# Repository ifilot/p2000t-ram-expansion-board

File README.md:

# P2000T RAM expansion board

## Table of contents

* [Purpose](#purpose)
* [Memory lay-out](#memory-lay-out)
* [Installation](#installation)
* [Testing the expansion board](#testing-the-expansion-board)
* [Schematic](#schematic)
* [Bill of materials](#bill-of-materials)
* [Testing bank switching in BASIC](#testing-bank-switching-in-basic)
* [Files](#files)
* [Alternative RAM expansions](#alternative-ram-expansions)
  * [SMD-128KiB version](#smd-128kib-version)
  * [SMD-CPLD-128KiB version](#smd-cpld-128kib-version)
  * [SMD-CPLD-512KiB version](#smd-cpld-512kib-version)
  * [THT-1056 KiB expansion](#tht-1056-kib-expansion)
  * [THT-2080 KiB expansion](#tht-2080-kib-expansion)
* [License](#license)

> [!TIP] 
> Have questions or comments about the **P2000T RAM expansion**? Join
> the conversation and chat with the developers on our [Discord
> server](https://discord.gg/YtzJTWYAxy).

## Purpose

This repository provides several RAM expansion boards for the Philips P2000T,
ranging from 64 KiB to over 2 MiB. Options vary in complexity (THT, SMD, CPLD),
so choose a board that fits your soldering skills and tools. A RAM tester
utility is included to verify proper installation and functionality after
assembly.

> [!IMPORTANT]
> This repository includes various RAM expansion PCBs for the P2000T. Your
> choice should depend on your soldering skills (THT or SMD) and available
> tools (e.g. CPLD programmer). Review this README to find a board that
> matches your comfort level before starting a build. 

## Memory lay-out

The memory lay-out of the P2000T is organized as shown in the table below

| Address       | Description      |
| ------------- | ---------------- |
| 0x0000-0x1000 | Monitor rom      |
| 0x1000-0x4FFF | Cartridge        |
| 0x5000-0x5FFF | Video memory     |
| 0x6000-0x9FFF | RAM memory       |
| 0xA000-0xDFFF | 16 KiB expansion |
| 0xE000-0xFFFF | 8 KiB banks      |

For the default 16 KiB stock model, only the memory at `0x6000-0x9FFF` is
available. The most simple expansion board adds 64k memory such that an
additional 16 KiB of RAM is available at `0xA000-0xDFFF` and another 48 KiB
using bank switching. Bank switching means that you can only access 8 KiB of the
48 KiB at a time, depending on the value of a register which can be accessed via
an `OUT` instruction at `0x94`. This register can hold values of `0-5`,
amounting to 6x8 KiB = 48 KiB of bankable memory.

## Installation

To install the expansion board, you need to plug in the expansion board on the
corresponding expansion 2x20 male pin header on the male board. This pin header
is found directly behind the cartridge slots. Furthermore, you need to solder
a GND and a 5V line onto the power PCB (see image below) and insert that in the
screw terminal of the expansion board.

> [!WARNING]  
> Please check carefully that the polarity is correct. Although the board comes
> with reverse polarity protection in the form of a diode, it is always better
> to check twice before turning on the power.

In the image below, you see a GND (black) and a 5V (red) line attached to the
power PCB. Please ensure you solder the lines to the correct pins and check
with a multimeter before connecting to the RAM expansion board.

Consult the image below for the correct voltages between the pins.

> [!WARNING]  
> Please check with a multimeter that you did not short-circuit any of the power
> lines on the POWER PCB. Please check this at least two times before turning on
> your P2000T. Short-circuiting of any of the power rails can cause permanent
> damage your machine.

## Testing the expansion board

This repository comes bundled with a RAM testing utility. Write the RAM testing
utility to a SLOT1 cartridge and boot your P2000T with this program in SLOT1.
The RAM testing utility will perform an extensive test of the memory and show
any errors it encounters.

## Schematic

The schematic for the RAM expansion board is shown below. The ram expansion
board essentially hosts two 32 KiB RAM chips and a bank register. Using a small
set of additional logic chips, the line decoding and bank switching is handled.

## Bill of materials

* 1x74HC00 (quad NAND-gate)
* 1x74HC04 (hex inverter)
* 1x74HC32 (quad OR-gate)
* 1x74HC157 (quad 2-input multiplexer)
* 1x74HC173 (quad positive edge triggered D-type flip-flop)
* 1x74HC688 (8-bit magnitude comparator)
* 1x74HC245 (octal bus transceiver)
* 2x62256 (32 KiB SRAM)
* 1x220uF capacitor (100uF also works)
* 8x0.1uF capacitor
* 1x1N4148 diode
* 1x 40 pin female pin header (2x20 pins; 2.54mm spacing)
* 1x screw terminal

**Unpopulated PCB**

**Populated PCB**

## Testing bank switching in BASIC

If you want to test the bank switching functionality in BASIC, you can use
the following instructions after booting the machine.

First, we need to set the top of BASIC to `0x9000`.

```
CLEAR 50,&H9000
```

The reason we do this is to ensure that the stack is not residing at the top 8
KiB because those bytes will become inaccessible after bank switching. Next, we
will first write a value to memory address `0xE000`, check that this value is
properly written, change to another bank and read from the same memory address.
A different value should be returned (typically 0). Next, we write a different
value to the `0xE000` and change bank to the initial bank. The original value
should now be correctly retrieved. The procedure is performed using the
following (very small) snippet of BASIC code.

```
10 POKE &HE000,42
20 PRINT(PEEK(&HE000))
30 OUT &H94,1
40 PRINT(PEEK(&HE000))
50 POKE &HE000,43
60 OUT &H94,0
70 PRINT(PEEK(&HE000))
```
After entering in these instructions, type `RUN`. The output of this code should
be something similar to the code as shown below. The second value might be
potentially different, depending on earlier memory operations, though is
expected to be a zero on a fresh boot of the machine.

```
42
0
42
```

## Files

* [KiCad schematics](pcb/p2000t-ram-expansion-board)
* [RAM tester utility](ramtester)

## Alternative RAM expansions

### SMD-128KiB version

Next to the 64 KiB memory expansion using
[DIP](https://en.wikipedia.org/wiki/Dual_in-line_package) chips, there is also a
128 KiB memory expansion using
[SMD](https://en.wikipedia.org/wiki/Surface-mount_technology) chips. Because of
the typical lower price of this last category of chips, this memory expansion is
a bit cheaper to produce. It does require you to be proficient in soldering on
SMD components.

The 128 KiB memory expansion uses a single `CY62128ELL-45SX` 128 KiB memory
chip. The lower 16 KiB of this chip can be accessed at `0xA000-0xDFFF`. The
remaining 112 KiB are available as 14 banks of 8 KiB each at `0xE000-0xFFFF`.
Similar to the other memory expansion boards, bank switching proceeds by writing
a value to I/O port `0x94`. One can also read back the current bank from this
port.

The source files for this board can be found
[here](pcb/p2000t-ram-expansion-board-128kb-smd/).

**Unpopulated PCB**

**Populated PCB**

**Installed PCB**

### SMD-CPLD-128KiB version

To cut down costs even further, there is also a CUPL version. Besides the
`CY62128ELL-45SX`, the PCB only hosts one other chip: a `ATF1502`. All glue
logic required for the RAM expansion board is basically programmed on this chip.

The source files for this board can be found
[here](pcb/p2000t-ram-expansion-board-128-512-smd-cpld).

**Unpopulated PCB**

**Populated PCB**

### SMD-CPLD-512KiB version

Moving beyond the 128 KiB limit, there is also a versatile SMD-type board
that admits 1-4 `CY62128ELL-45SX` 128 KiB memory chips.

The source files for this board can be found
[here](pcb/p2000t-ram-expansion-board-128-512-smd-cpld).

**Installed PCB**

**Populated PCB**

### THT-1056 KiB expansion

This board uses a single 32 KiB static RAM chip to provide 2x16 KiB on
`0xA000-0xDFFF` and two 512 KiB static RAM chips to provide another 128x8 KiB on
`0xE000-0xFFFF`. The way this board works is very similar to the regular 64 KiB
board. The highest bit in the bank register toggle the 16 KiB banking while the
lower 7 bits provide the banking for the 8 KiB of memory.

The source files for this board can be found
[here](pcb/p2000t-ram-expansion-board-1056kb/).

**Unpopulated PCB**

**Populated PCB**

**Installed PCB**

### THT-2080 KiB expansion

This board uses a single 32 KiB static RAM chip to provide 2x16 KiB on
`0xA000-0xDFFF` and four 512 KiB static RAM chips to provide another 256x8 KiB
on `0xE000-0xFFFF`. This board requires two bank registers, one 8-bit bank
register exposed on I/O port `0x94` and another two-bit bank register on I/O
port `0x95` (only one bit of the two-bit bank register is used).

The source files for this board can be found
[here](pcb/p2000t-ram-expansion-board-2080kb/).

**Populated PCB**

**Installed PCB**

## License

* All source code, i.e. the [ram tester utility](ramtester)
  are released under a [GPLv3 license](https://www.gnu.org/licenses/gpl-3.0.html).
* The hardware files (KiCad schematics) are released under the 
  [CC BY-SA 4.0](https://creativecommons.org/licenses/by-sa/4.0/) license.

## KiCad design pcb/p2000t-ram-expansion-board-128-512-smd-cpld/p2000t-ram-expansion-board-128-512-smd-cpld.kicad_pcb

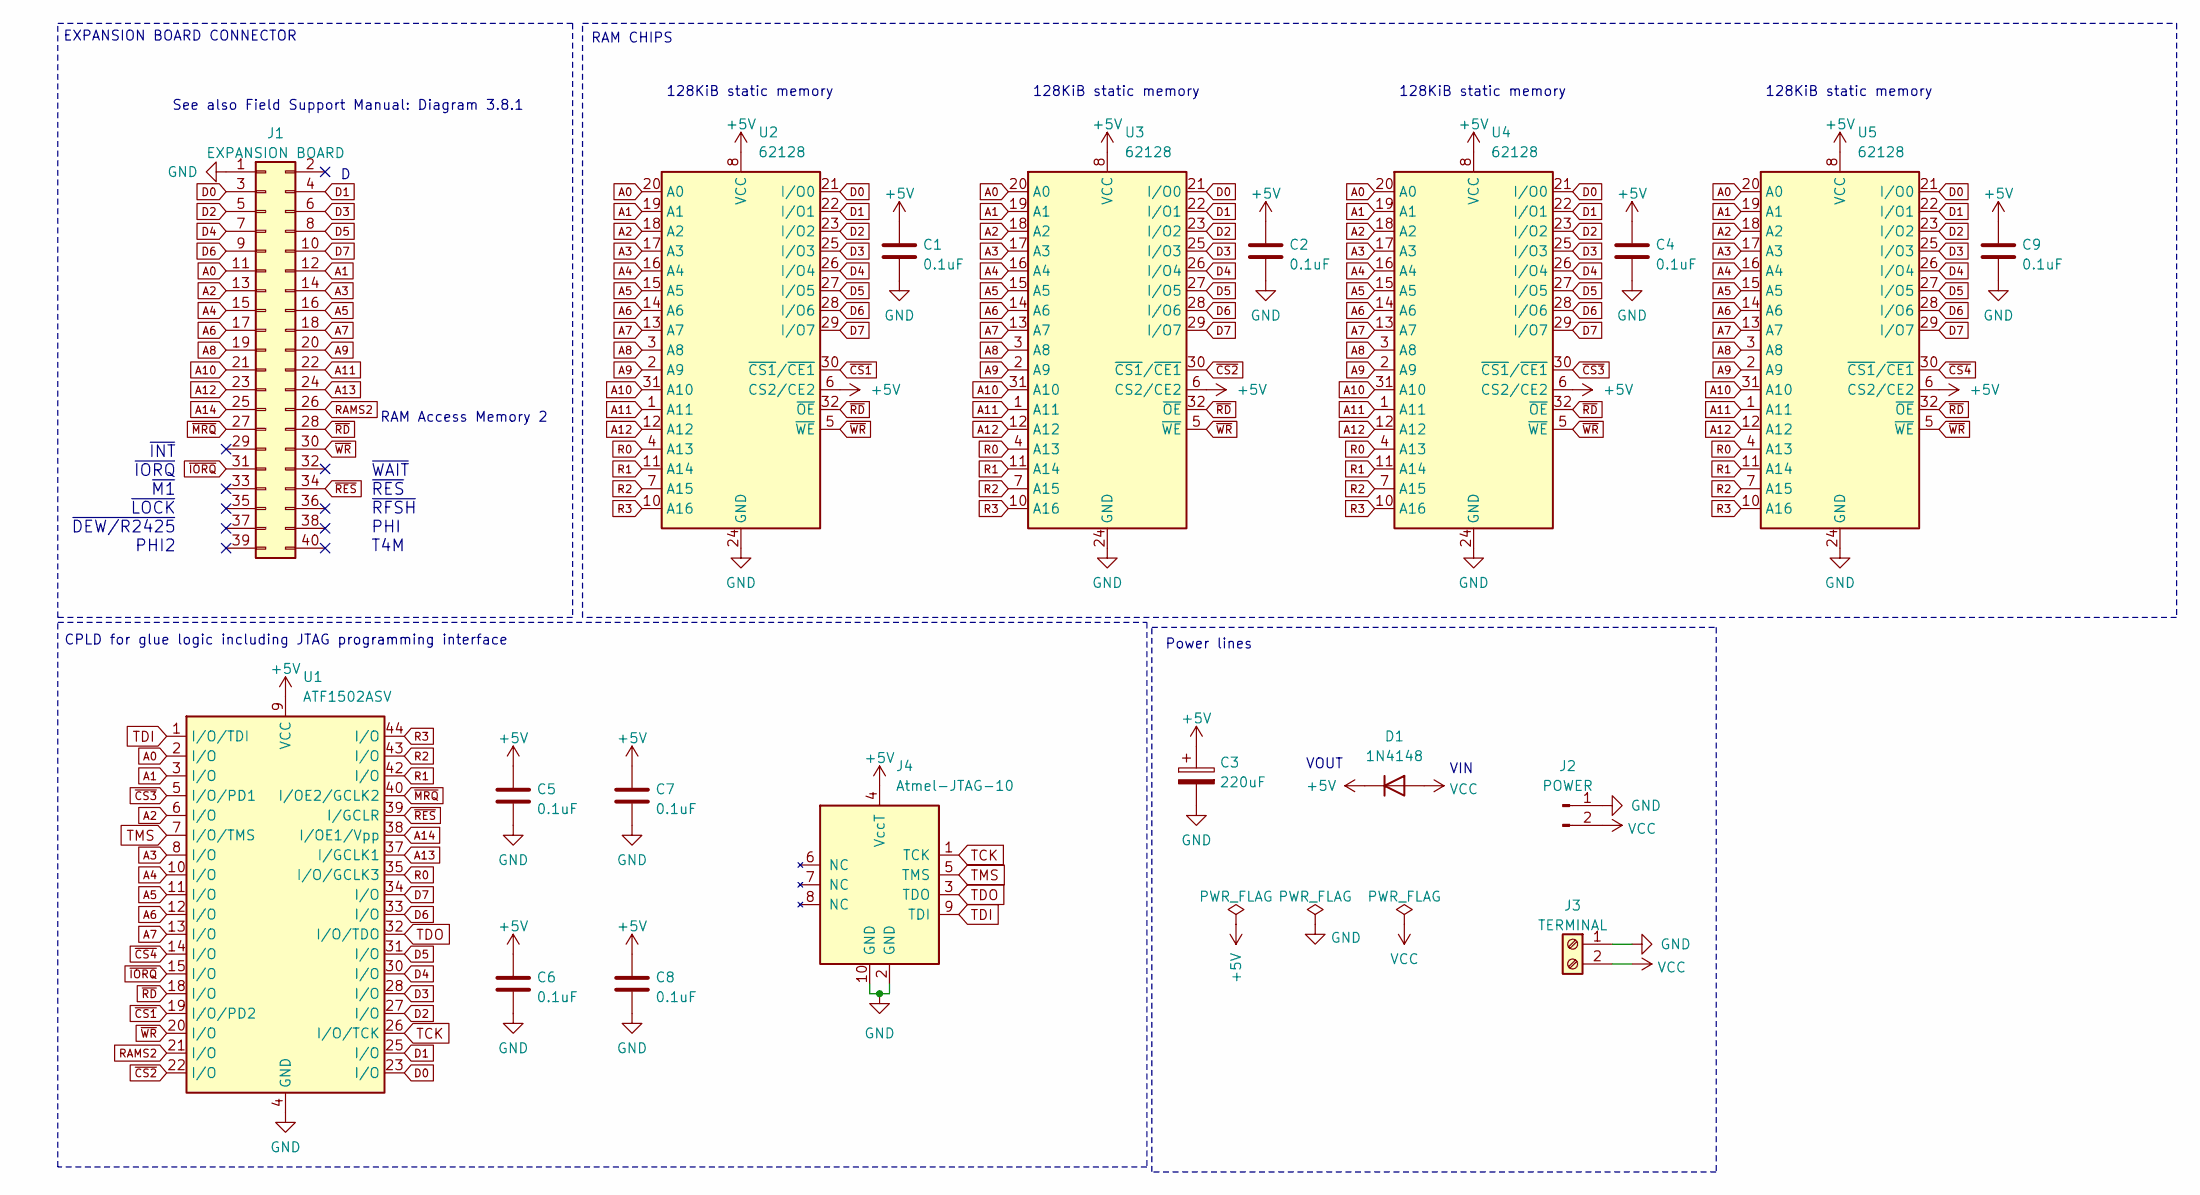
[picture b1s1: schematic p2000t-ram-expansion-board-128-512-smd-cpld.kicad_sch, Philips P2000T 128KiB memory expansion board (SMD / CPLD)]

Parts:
C1, C2, C4, C5, C6, C7, C8, C9: 0.1uF; C_0805_2012Metric_Pad1.18x1.45mm_HandSolder; LCSC Part # C126469
C3: 220uF; CP_Radial_D6.3mm_P2.50mm
D1: 1N4148; D_DO-35_SOD27_P7.62mm_Horizontal
J1: EXPANSION BOARD; PinHeader_2x20_P2.54mm_Vertical
J2: POWER; PinSocket_1x02_P2.54mm_Vertical
J3: TERMINAL; TerminalBlock_bornier-2_P5.08mm
J4: Atmel-JTAG-10; IDC-Header_2x05_P2.54mm_Vertical
U1: ATF1502ASV; TQFP-44_10x10mm_P0.8mm
U2, U3, U4, U5: 62128; TSOP-I-32_18.4x8mm_P0.5mm; LCSC Part # C2840304

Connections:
+5V: C1.1, C2.1, C3.1, C4.1, C5.1, C6.1, C7.1, C8.1, C9.1, D1.1 (K), J4.4 (VccT), U1.9 (VCC), U1.17 (VCC), U1.29 (VCC), U1.41 (VCC), U2.6 (CS2/CE2), U2.8 (VCC), U3.6 (CS2/CE2), U3.8 (VCC), U4.6 (CS2/CE2), U4.8 (VCC), U5.6 (CS2/CE2), U5.8 (VCC)
A0: J1.11, U1.2 (I/O), U2.20 (A0), U3.20 (A0), U4.20 (A0), U5.20 (A0)
A1: J1.12, U1.3 (I/O), U2.19 (A1), U3.19 (A1), U4.19 (A1), U5.19 (A1)
A2: J1.13, U1.6 (I/O), U2.18 (A2), U3.18 (A2), U4.18 (A2), U5.18 (A2)
A3: J1.14, U1.8 (I/O), U2.17 (A3), U3.17 (A3), U4.17 (A3), U5.17 (A3)
A4: J1.15, U1.10 (I/O), U2.16 (A4), U3.16 (A4), U4.16 (A4), U5.16 (A4)
A5: J1.16, U1.11 (I/O), U2.15 (A5), U3.15 (A5), U4.15 (A5), U5.15 (A5)
A6: J1.17, U1.12 (I/O), U2.14 (A6), U3.14 (A6), U4.14 (A6), U5.14 (A6)
A7: J1.18, U1.13 (I/O), U2.13 (A7), U3.13 (A7), U4.13 (A7), U5.13 (A7)
A8: J1.19, U2.3 (A8), U3.3 (A8), U4.3 (A8), U5.3 (A8)
A9: J1.20, U2.2 (A9), U3.2 (A9), U4.2 (A9), U5.2 (A9)
A10: J1.21, U2.31 (A10), U3.31 (A10), U4.31 (A10), U5.31 (A10)
A11: J1.22, U2.1 (A11), U3.1 (A11), U4.1 (A11), U5.1 (A11)
A12: J1.23, U2.12 (A12), U3.12 (A12), U4.12 (A12), U5.12 (A12)
A13: J1.24, U1.37 (I/GCLK1)
A14: J1.25, U1.38 (I/OE1/Vpp)
D0: J1.3, U1.23 (I/O), U2.21 (I/O0), U3.21 (I/O0), U4.21 (I/O0), U5.21 (I/O0)
D1: J1.4, U1.25 (I/O), U2.22 (I/O1), U3.22 (I/O1), U4.22 (I/O1), U5.22 (I/O1)
D2: J1.5, U1.27 (I/O), U2.23 (I/O2), U3.23 (I/O2), U4.23 (I/O2), U5.23 (I/O2)
D3: J1.6, U1.28 (I/O), U2.25 (I/O3), U3.25 (I/O3), U4.25 (I/O3), U5.25 (I/O3)
D4: J1.7, U1.30 (I/O), U2.26 (I/O4), U3.26 (I/O4), U4.26 (I/O4), U5.26 (I/O4)
D5: J1.8, U1.31 (I/O), U2.27 (I/O5), U3.27 (I/O5), U4.27 (I/O5), U5.27 (I/O5)
D6: J1.9, U1.33 (I/O), U2.28 (I/O6), U3.28 (I/O6), U4.28 (I/O6), U5.28 (I/O6)
D7: J1.10, U1.34 (I/O), U2.29 (I/O7), U3.29 (I/O7), U4.29 (I/O7), U5.29 (I/O7)
GND: C1.2, C2.2, C3.2, C4.2, C5.2, C6.2, C7.2, C8.2, C9.2, J1.1, J2.1, J3.1, J4.2 (GND), J4.10 (GND), U1.4 (GND), U1.16 (GND), U1.24 (GND), U1.36 (GND), U2.24 (GND), U3.24 (GND), U4.24 (GND), U5.24 (GND)
R0: U1.35 (I/O/GCLK3), U2.4 (A13), U3.4 (A13), U4.4 (A13), U5.4 (A13)
R1: U1.42 (I/O), U2.11 (A14), U3.11 (A14), U4.11 (A14), U5.11 (A14)
R2: U1.43 (I/O), U2.7 (A15), U3.7 (A15), U4.7 (A15), U5.7 (A15)
R3: U1.44 (I/O), U2.10 (A16), U3.10 (A16), U4.10 (A16), U5.10 (A16)
RAMS2: J1.26, U1.21 (I/O)
TCK: J4.1 (TCK), U1.26 (I/O/TCK)
TDI: J4.9 (TDI), U1.1 (I/O/TDI)
TDO: J4.3 (TDO), U1.32 (I/O/TDO)
TMS: J4.5 (TMS), U1.7 (I/O/TMS)
VCC: D1.2 (A), J2.2, J3.2
~CS1: U1.19 (I/O/PD2), U2.30 (~CS1/~CE1)
~CS2: U1.22 (I/O), U3.30 (~CS1/~CE1)
~CS3: U1.5 (I/O/PD1), U4.30 (~CS1/~CE1)
~CS4: U1.14 (I/O), U5.30 (~CS1/~CE1)
~IORQ: J1.31, U1.15 (I/O)
~MRQ: J1.27, U1.40 (I/OE2/GCLK2)
~RD: J1.28, U1.18 (I/O), U2.32 (~OE), U3.32 (~OE), U4.32 (~OE), U5.32 (~OE)
~RES: J1.34, U1.39 (I/GCLR)
~WR: J1.30, U1.20 (I/O), U2.5 (~WE), U3.5 (~WE), U4.5 (~WE), U5.5 (~WE)

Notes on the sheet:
128KiB static memory
VIN
EXPANSION BOARD CONNECTOR
VOUT
~{INT} ~{IORQ} ~{M1} ~{LOCK} ~{DEW/R2425} PHI2
RAM Access Memory 2
RAM CHIPS
See also Field Support Manual: Diagram 3.8.1
Power lines
~{WAIT} ~{RES} ~{RFSH} PHI T4M
CPLD for glue logic including JTAG programming interface

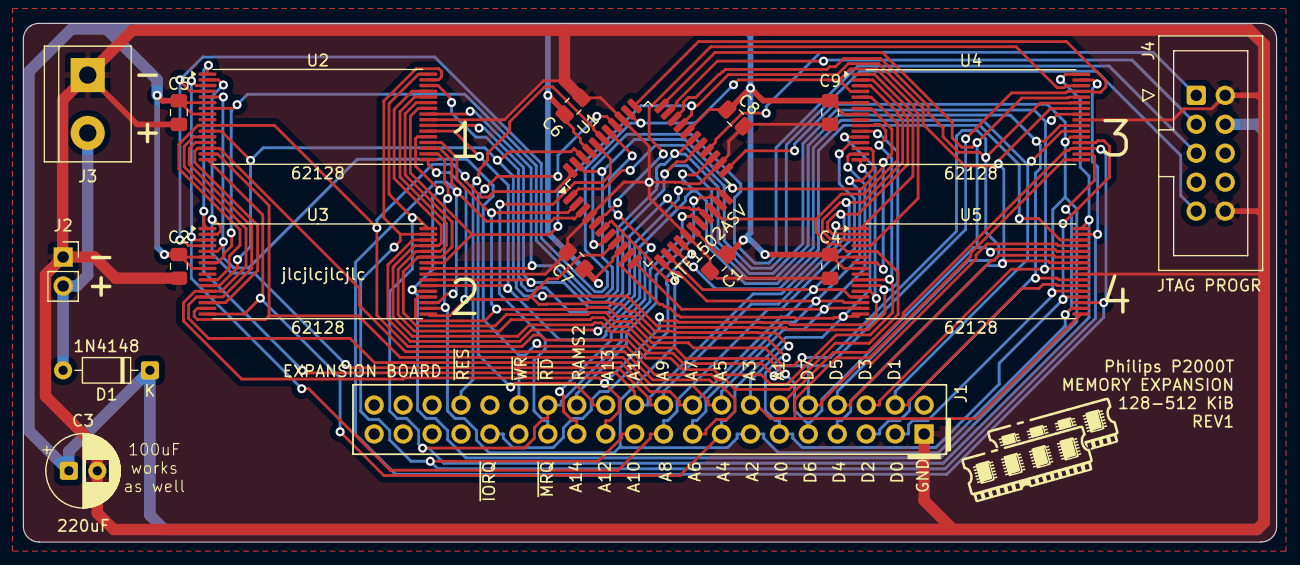
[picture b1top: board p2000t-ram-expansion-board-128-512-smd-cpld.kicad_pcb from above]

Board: 2 copper layers, 110.0 x 45.5 mm, 19 parts (1 on the bottom side), 44 nets.

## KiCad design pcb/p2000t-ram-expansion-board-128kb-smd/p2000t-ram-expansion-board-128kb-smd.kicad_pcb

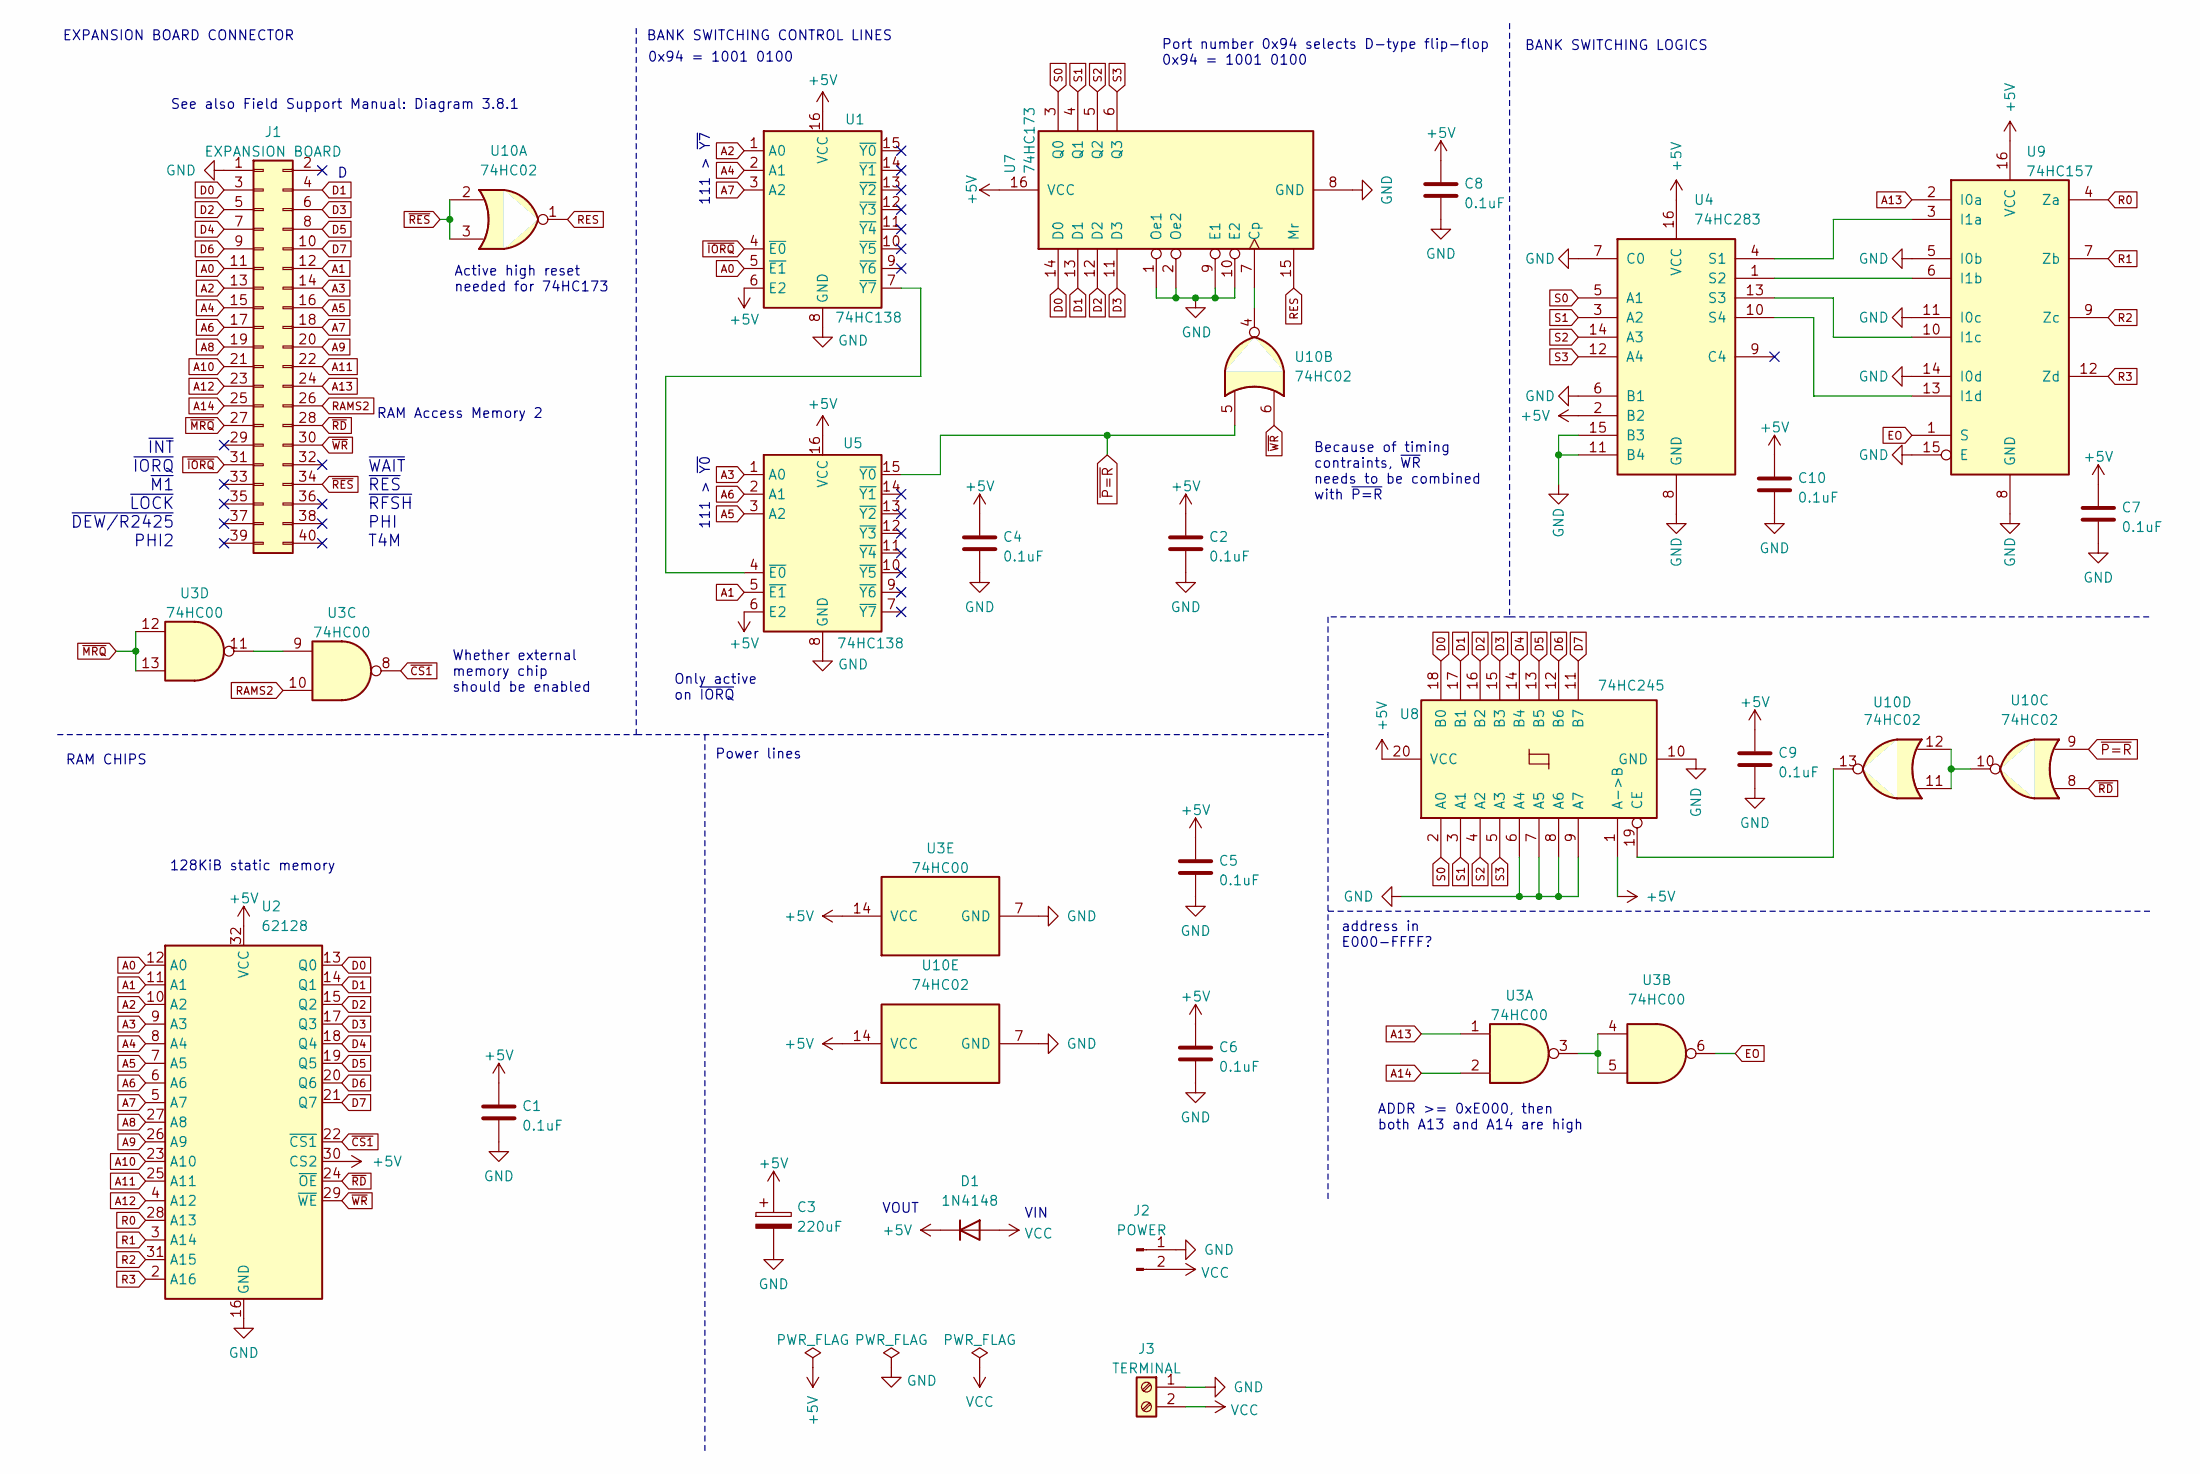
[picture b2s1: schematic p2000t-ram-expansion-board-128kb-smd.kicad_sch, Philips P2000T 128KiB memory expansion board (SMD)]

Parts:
C1, C2, C4, C5, C6, C7, C8, C9, C10: 0.1uF; C_0805_2012Metric_Pad1.18x1.45mm_HandSolder; LCSC Part # C126469
C3: 220uF; CP_Radial_D6.3mm_P2.50mm
D1: 1N4148; D_DO-35_SOD27_P7.62mm_Horizontal
J1: EXPANSION BOARD; PinHeader_2x20_P2.54mm_Vertical
J2: POWER; PinSocket_1x02_P2.54mm_Vertical
J3: TERMINAL; TerminalBlock_bornier-2_P5.08mm
U1, U5: 74HC138; SOIC-16_3.9x9.9mm_P1.27mm; LCSC Part # C5602
U2: 62128; SSOP-32_11.305x20.495mm_P1.27mm; LCSC Part # C2840304
U3: 74HC00; SOIC-14_3.9x8.7mm_P1.27mm; LCSC Part # C699445
U4: 74HC283; SOIC-16_3.9x9.9mm_P1.27mm; LCSC Part # C543032
U7: 74HC173; SOIC-16_3.9x9.9mm_P1.27mm; LCSC Part # C546651
U8: 74HC245; SOIC-20W_7.5x12.8mm_P1.27mm; LCSC Part # C5625
U9: 74HC157; SOIC-16_3.9x9.9mm_P1.27mm; LCSC Part # C6823
U10: 74HC02; SOIC-14_3.9x8.7mm_P1.27mm; LCSC Part # C5588

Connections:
+5V: C1.1, C2.1, C3.1, C4.1, C5.1, C6.1, C7.1, C8.1, C9.1, C10.1, D1.1 (K), U1.6 (E2), U1.16 (VCC), U2.30 (CS2), U2.32 (VCC), U3.14 (VCC), U4.2 (B2), U4.16 (VCC), U5.6 (E2), U5.16 (VCC), U7.16 (VCC), U8.1 (A->B), U8.20 (VCC), U9.16 (VCC), U10.14 (VCC)
A0: J1.11, U1.5 (~E1), U2.12 (A0)
A1: J1.12, U2.11 (A1), U5.5 (~E1)
A2: J1.13, U1.1 (A0), U2.10 (A2)
A3: J1.14, U2.9 (A3), U5.1 (A0)
A4: J1.15, U1.2 (A1), U2.8 (A4)
A5: J1.16, U2.7 (A5), U5.3 (A2)
A6: J1.17, U2.6 (A6), U5.2 (A1)
A7: J1.18, U1.3 (A2), U2.5 (A7)
A8: J1.19, U2.27 (A8)
A9: J1.20, U2.26 (A9)
A10: J1.21, U2.23 (A10)
A11: J1.22, U2.25 (A11)
A12: J1.23, U2.4 (A12)
A13: J1.24, U3.1, U9.2 (I0a)
A14: J1.25, U3.2
D0: J1.3, U2.13 (Q0), U7.14 (D0), U8.18 (B0)
D1: J1.4, U2.14 (Q1), U7.13 (D1), U8.17 (B1)
D2: J1.5, U2.15 (Q2), U7.12 (D2), U8.16 (B2)
D3: J1.6, U2.17 (Q3), U7.11 (D3), U8.15 (B3)
D4: J1.7, U2.18 (Q4), U8.14 (B4)
D5: J1.8, U2.19 (Q5), U8.13 (B5)
D6: J1.9, U2.20 (Q6), U8.12 (B6)
D7: J1.10, U2.21 (Q7), U8.11 (B7)
EO: U3.6, U9.1 (S)
GND: C1.2, C2.2, C3.2, C4.2, C5.2, C6.2, C7.2, C8.2, C9.2, C10.2, J1.1, J2.1, J3.1, U1.8 (GND), U2.16 (GND), U3.7 (GND), U4.6 (B1), U4.7 (C0), U4.8 (GND), U4.11 (B4), U4.15 (B3), U5.8 (GND), U7.1 (Oe1), U7.2 (Oe2), U7.8 (GND), U7.9 (E1), U7.10 (E2), U8.6 (A4), U8.7 (A5), U8.8 (A6), U8.9 (A7), U8.10 (GND), U9.5 (I0b), U9.8 (GND), U9.11 (I0c), U9.14 (I0d), U9.15 (E), U10.7 (GND)
unnamed: U1.7 (~Y7), U5.4 (~E0)
unnamed: U3.3, U3.4, U3.5
unnamed: U3.9, U3.11
unnamed: U4.4 (S1), U9.3 (I1a)
unnamed: U4.1 (S2), U9.6 (I1b)
unnamed: U4.13 (S3), U9.10 (I1c)
unnamed: U4.10 (S4), U9.13 (I1d)
unnamed: U7.7 (Cp), U10.4
unnamed: U8.19 (CE), U10.13
unnamed: U10.10, U10.11, U10.12
R0: U2.28 (A13), U9.4 (Za)
R1: U2.3 (A14), U9.7 (Zb)
R2: U2.31 (A15), U9.9 (Zc)
R3: U2.2 (A16), U9.12 (Zd)
RAMS2: J1.26, U3.10
RES: U7.15 (Mr), U10.1
S0: U4.5 (A1), U7.3 (Q0), U8.2 (A0)
S1: U4.3 (A2), U7.4 (Q1), U8.3 (A1)
S2: U4.14 (A3), U7.5 (Q2), U8.4 (A2)
S3: U4.12 (A4), U7.6 (Q3), U8.5 (A3)
VCC: D1.2 (A), J2.2, J3.2
~CS1: U2.22 (~CS1), U3.8
~IORQ: J1.31, U1.4 (~E0)
~MRQ: J1.27, U3.12, U3.13
~P=R: U5.15 (~Y0), U10.5, U10.9
~RD: J1.28, U2.24 (~OE), U10.8
~RES: J1.34, U10.2, U10.3
~WR: J1.30, U2.29 (~WE), U10.6

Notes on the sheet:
VIN
EXPANSION BOARD CONNECTOR
VOUT
0x94 = 1001 0100
~{INT} ~{IORQ} ~{M1} ~{LOCK} ~{DEW/R2425} PHI2
Only active on ~{IORQ}
RAM Access Memory 2
111 > ~{Y0}
address in E000-FFFF?
111 > ~{Y7}
Because of timing contraints, ~{WR} needs to be combined with ~{P=R}
BANK SWITCHING LOGICS
RAM CHIPS
See also Field Support Manual: Diagram 3.8.1
Power lines
BANK SWITCHING CONTROL LINES
128KiB static memory
ADDR >= 0xE000, then both A13 and A14 are high
~{WAIT} ~{RES} ~{RFSH} PHI T4M
Active high reset needed for 74HC173
Whether external memory chip should be enabled
Port number 0x94 selects D-type flip-flop 0x94 = 1001 0100

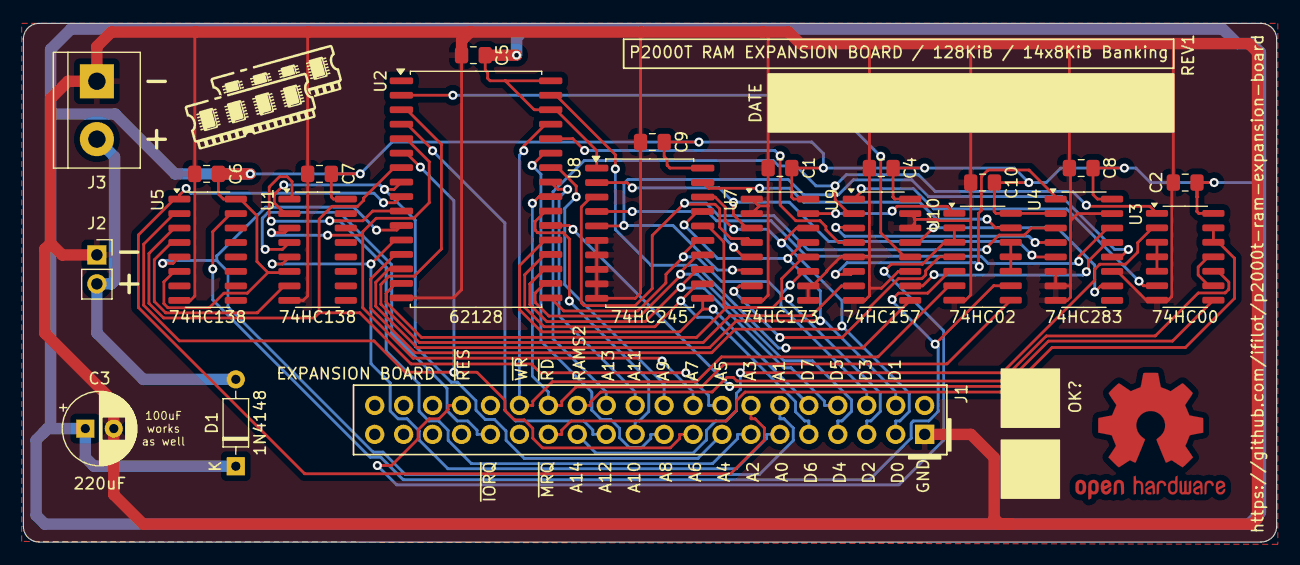
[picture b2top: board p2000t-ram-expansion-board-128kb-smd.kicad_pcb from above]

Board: 2 copper layers, 110.0 x 45.5 mm, 24 parts (1 on the bottom side), 54 nets.

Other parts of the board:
LOGO1: OSHW-Logo2_14.6x12mm_Copper_AND_Mask

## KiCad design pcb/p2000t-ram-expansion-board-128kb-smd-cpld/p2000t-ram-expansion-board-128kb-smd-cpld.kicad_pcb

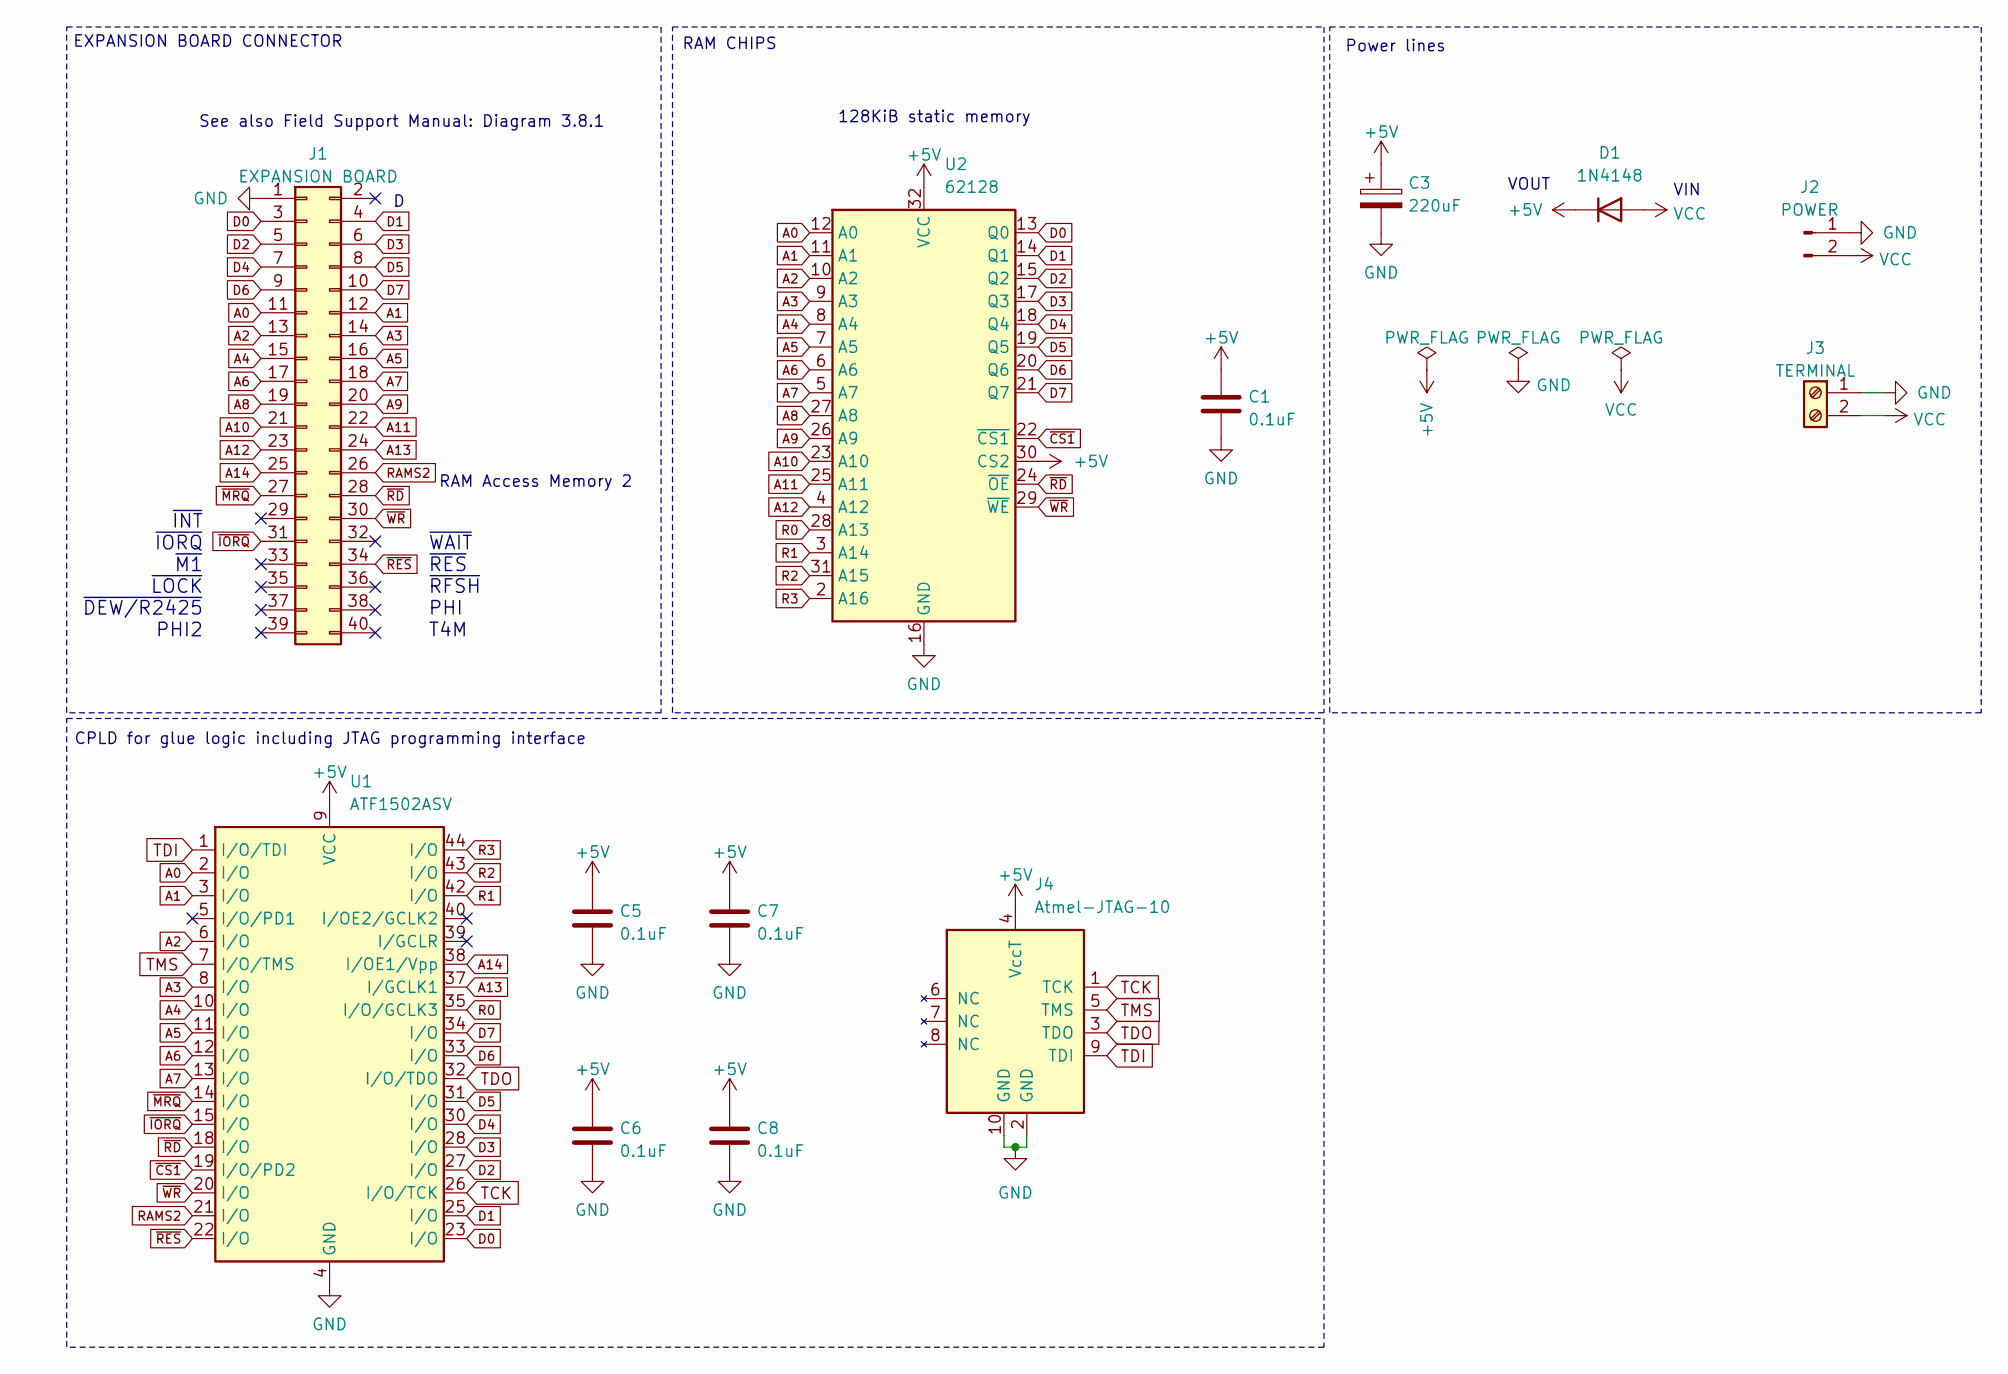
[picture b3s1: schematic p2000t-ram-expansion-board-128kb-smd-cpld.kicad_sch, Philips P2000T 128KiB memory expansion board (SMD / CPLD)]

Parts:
C1, C5, C6, C7, C8: 0.1uF; C_0805_2012Metric_Pad1.18x1.45mm_HandSolder; LCSC Part # C126469
C3: 220uF; CP_Radial_D6.3mm_P2.50mm
D1: 1N4148; D_DO-35_SOD27_P7.62mm_Horizontal
J1: EXPANSION BOARD; PinHeader_2x20_P2.54mm_Vertical
J2: POWER; PinSocket_1x02_P2.54mm_Vertical
J3: TERMINAL; TerminalBlock_bornier-2_P5.08mm
J4: Atmel-JTAG-10; IDC-Header_2x05_P2.54mm_Vertical
U1: ATF1502ASV; TQFP-44_10x10mm_P0.8mm
U2: 62128; SSOP-32_11.305x20.495mm_P1.27mm; LCSC Part # C2840304

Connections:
+5V: C1.1, C3.1, C5.1, C6.1, C7.1, C8.1, D1.1 (K), J4.4 (VccT), U1.9 (VCC), U1.17 (VCC), U1.29 (VCC), U1.41 (VCC), U2.30 (CS2), U2.32 (VCC)
A0: J1.11, U1.2 (I/O), U2.12 (A0)
A1: J1.12, U1.3 (I/O), U2.11 (A1)
A2: J1.13, U1.6 (I/O), U2.10 (A2)
A3: J1.14, U1.8 (I/O), U2.9 (A3)
A4: J1.15, U1.10 (I/O), U2.8 (A4)
A5: J1.16, U1.11 (I/O), U2.7 (A5)
A6: J1.17, U1.12 (I/O), U2.6 (A6)
A7: J1.18, U1.13 (I/O), U2.5 (A7)
A8: J1.19, U2.27 (A8)
A9: J1.20, U2.26 (A9)
A10: J1.21, U2.23 (A10)
A11: J1.22, U2.25 (A11)
A12: J1.23, U2.4 (A12)
A13: J1.24, U1.37 (I/GCLK1)
A14: J1.25, U1.38 (I/OE1/Vpp)
D0: J1.3, U1.23 (I/O), U2.13 (Q0)
D1: J1.4, U1.25 (I/O), U2.14 (Q1)
D2: J1.5, U1.27 (I/O), U2.15 (Q2)
D3: J1.6, U1.28 (I/O), U2.17 (Q3)
D4: J1.7, U1.30 (I/O), U2.18 (Q4)
D5: J1.8, U1.31 (I/O), U2.19 (Q5)
D6: J1.9, U1.33 (I/O), U2.20 (Q6)
D7: J1.10, U1.34 (I/O), U2.21 (Q7)
GND: C1.2, C3.2, C5.2, C6.2, C7.2, C8.2, J1.1, J2.1, J3.1, J4.2 (GND), J4.10 (GND), U1.4 (GND), U1.16 (GND), U1.24 (GND), U1.36 (GND), U2.16 (GND)
R0: U1.35 (I/O/GCLK3), U2.28 (A13)
R1: U1.42 (I/O), U2.3 (A14)
R2: U1.43 (I/O), U2.31 (A15)
R3: U1.44 (I/O), U2.2 (A16)
RAMS2: J1.26, U1.21 (I/O)
TCK: J4.1 (TCK), U1.26 (I/O/TCK)
TDI: J4.9 (TDI), U1.1 (I/O/TDI)
TDO: J4.3 (TDO), U1.32 (I/O/TDO)
TMS: J4.5 (TMS), U1.7 (I/O/TMS)
VCC: D1.2 (A), J2.2, J3.2
~CS1: U1.19 (I/O/PD2), U2.22 (~CS1)
~IORQ: J1.31, U1.15 (I/O)
~MRQ: J1.27, U1.14 (I/O)
~RD: J1.28, U1.18 (I/O), U2.24 (~OE)
~RES: J1.34, U1.22 (I/O)
~WR: J1.30, U1.20 (I/O), U2.29 (~WE)

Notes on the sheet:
VIN
EXPANSION BOARD CONNECTOR
VOUT
~{INT} ~{IORQ} ~{M1} ~{LOCK} ~{DEW/R2425} PHI2
RAM Access Memory 2
RAM CHIPS
See also Field Support Manual: Diagram 3.8.1
Power lines
128KiB static memory
~{WAIT} ~{RES} ~{RFSH} PHI T4M
CPLD for glue logic including JTAG programming interface

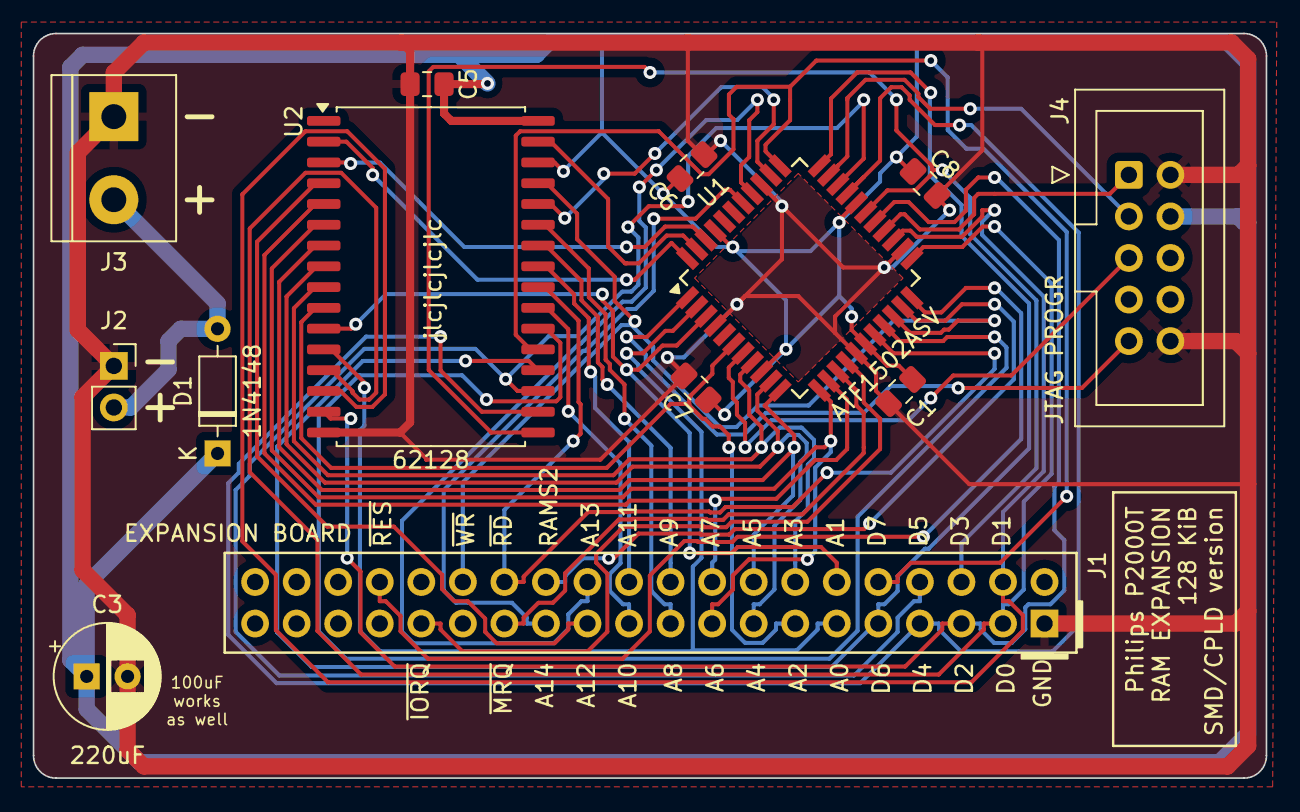
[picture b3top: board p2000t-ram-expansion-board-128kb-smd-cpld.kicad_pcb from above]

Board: 2 copper layers, 75.4 x 45.5 mm, 13 parts (1 on the bottom side), 41 nets.

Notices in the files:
README.md:
License: GPL v3
License: CC-BY-NC-SA-4.0
